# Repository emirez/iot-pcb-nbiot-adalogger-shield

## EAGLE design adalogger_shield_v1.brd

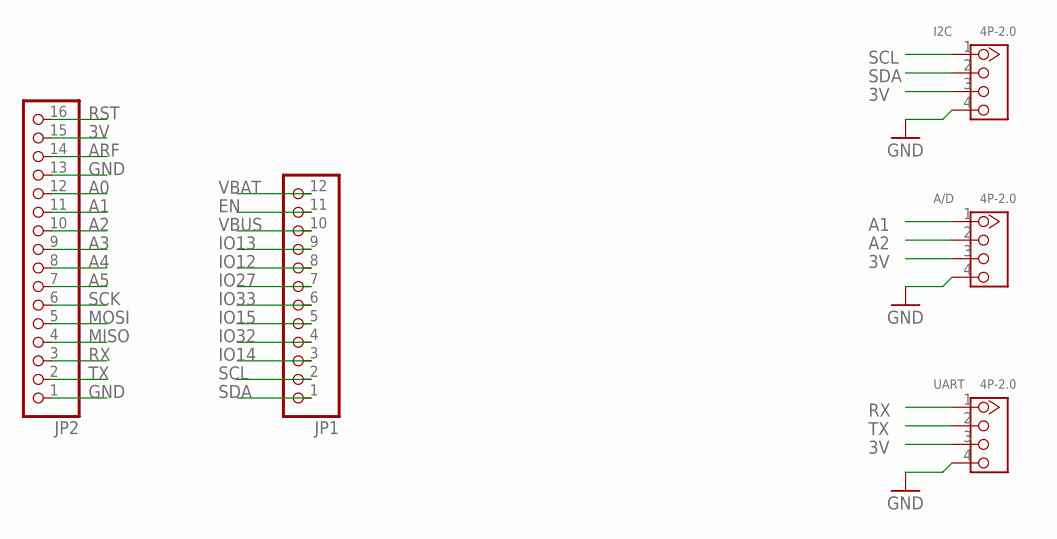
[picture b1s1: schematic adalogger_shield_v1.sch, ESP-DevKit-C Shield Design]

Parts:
A/D: 4P-2.0; HW4-2.0
I2C: 4P-2.0; HW4-2.0
JP1: HEADER-1X12; 1X12_ROUND
JP2: HEADER-1X16ROUND; 1X16_ROUND
UART: 4P-2.0; HW4-2.0

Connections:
3V: A/D.3, I2C.3, JP2.15, UART.3
A0: JP2.12
A1: A/D.1, JP2.11
A2: A/D.2, JP2.10
A3: JP2.9
A4: JP2.8
A5: JP2.7
ARF: JP2.14
EN: JP1.11
GND: A/D.4, I2C.4, JP2.1, JP2.13, UART.4
IO12: JP1.8
IO13: JP1.9
IO14: JP1.3
IO15: JP1.5
IO27: JP1.7
IO32: JP1.4
IO33: JP1.6
MISO: JP2.4
MOSI: JP2.5
RST: JP2.16
RX: JP2.3, UART.1
SCK: JP2.6
SCL: I2C.1, JP1.2
SDA: I2C.2, JP1.1
TX: JP2.2, UART.2
VBAT: JP1.12
VBUS: JP1.10

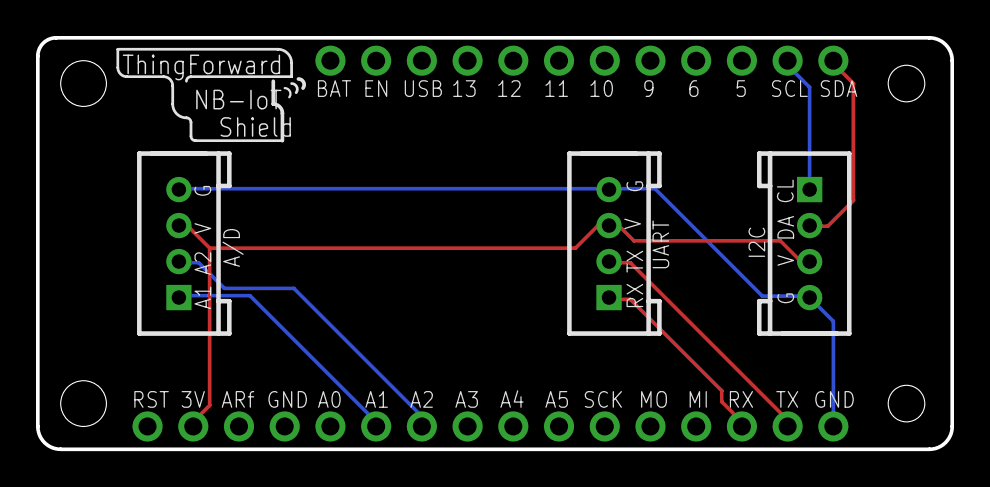
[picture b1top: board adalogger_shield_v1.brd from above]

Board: 2 copper layers, 50.8 x 22.9 mm, 5 parts (1 on the bottom side), 8 nets.

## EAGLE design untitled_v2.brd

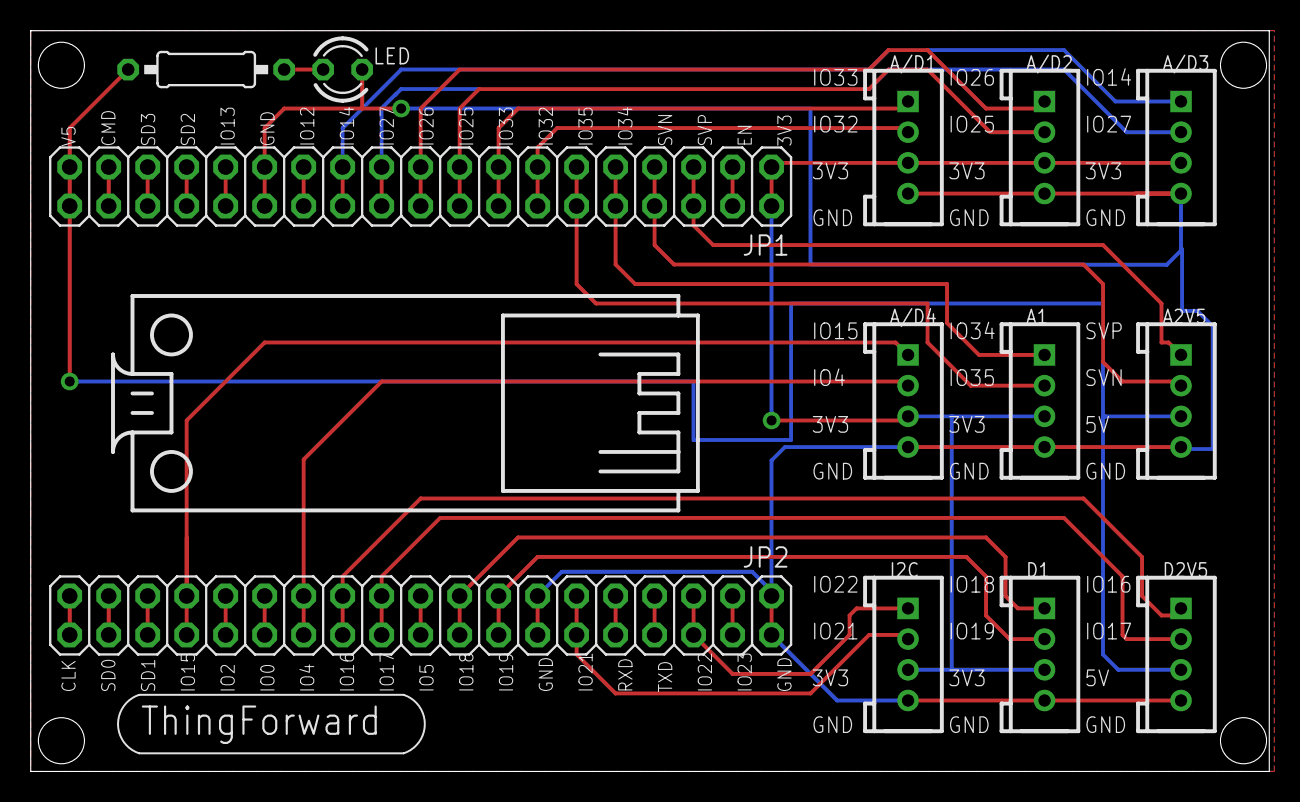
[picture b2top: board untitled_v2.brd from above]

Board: 2 copper layers, 80.7 x 48.2 mm, 14 parts (0 on the bottom side), 37 nets.

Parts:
A1, A2V5: 4P-2.0; HW4-2.0
A/D1, A/D2, A/D3, A/D4: 4P-2.0; HW4-2.0
D1, D2V5: 4P-2.0; HW4-2.0
I2C: 4P-2.0; HW4-2.0
JP1, JP2: 2X19
LED: LED3MM
R1: 1K; 0207/10
U$5: BREADBOARD_SPACING

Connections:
+3V3: A1.3, A/D1.3, A/D2.3, A/D3.3, A/D4.3, D1.3, I2C.3, JP1.1, JP1.2
+5V: A2V5.3, D2V5.3, JP1.37, JP1.38, R1.1
CLK: JP2.37, JP2.38
CMD: JP1.35, JP1.36
CRC: LED.A, R1.2
EN: JP1.3, JP1.4
GND: A1.4, A2V5.4, A/D1.4, A/D2.4, A/D3.4, A/D4.4, D1.4, D2V5.4, I2C.4, JP1.27, JP1.28, JP2.1, JP2.2, JP2.13, JP2.14, LED.K
IO0: JP2.27, JP2.28
IO2: JP2.29, JP2.30
IO4: A/D4.2, JP2.25, JP2.26
IO5: JP2.19, JP2.20
IO12: JP1.25, JP1.26
IO13: JP1.29, JP1.30
IO14: A/D3.1, JP1.23, JP1.24
IO15: A/D4.1, JP2.31, JP2.32
IO16: D2V5.1, JP2.23, JP2.24
IO17: D2V5.2, JP2.21, JP2.22
IO18: D1.1, JP2.17, JP2.18
IO19: D1.2, JP2.15, JP2.16
IO21: I2C.2, JP2.11, JP2.12
IO22: I2C.1, JP2.5, JP2.6
IO23: JP2.3, JP2.4
IO25: A/D2.2, JP1.17, JP1.18
IO26: A/D2.1, JP1.19, JP1.20
IO27: A/D3.2, JP1.21, JP1.22
IO32: A/D1.2, JP1.13, JP1.14
IO33: A/D1.1, JP1.15, JP1.16
IO34: A1.1, JP1.9, JP1.10
IO35: A1.2, JP1.11, JP1.12
RX: JP2.9, JP2.10
SD0: JP2.35, JP2.36
SD1: JP2.33, JP2.34
SD2: JP1.31, JP1.32
SD3: JP1.33, JP1.34
SVN: A2V5.2, JP1.7, JP1.8
SVP: A2V5.1, JP1.5, JP1.6
TX: JP2.7, JP2.8

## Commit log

2018-01-23 second commit
2018-01-24 third commit
2018-01-24 end of design
2018-01-25 last commit
2018-08-24 renaming
2018-08-24 several updates
2018-08-27 dimensions ok
2018-08-27 routing ok
2018-08-27 everythings ok#
2018-08-28 test ok
2018-08-28 ready for production
2018-08-28 ready
2018-08-28 final version
2018-08-28 production photos
2018-09-04 holes update ok
2018-09-25 second version OK

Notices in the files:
parts and their libraries:
microbuilder: This work is placed in the public domain, and may be freely used for commercial and non-commercial work with the following conditions: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
SparkFun-Aesthetics: Licensing: Creative Commons ShareAlike 4.0 International - https://creativecommons.org/licenses/by-sa/4.0
